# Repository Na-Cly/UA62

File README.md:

# UA62
A Universal PCB for the atreus62 by profet23
#### Firmware availble on the qmk configurator or the qmk repo: 
* https://github.com/qmk/qmk_firmware
* https://config.qmk.fm/#/ua62/LAYOUT (default layout to come)
* no default layout, so grab the json layout and upload it if you want a base layout to start from.

#### Build tips
* Diode direction for through hole  

* The pro micro and diodes are soldered to the bottom of the pcb.  
 
### Changes
1. Added universal switch holes for MX/Alps, Matias/Choc
2. Added support for through-hole diodes
3. Fixed edge cuts: They were off center from the middle of the pcb.
4. Rounded the sharp corners.
5. Uncomplicated the trace layout.
6. Updated pinout for pro micro.
7. Updated Silkscreen.

Uses MIT licensed footprints originally sourced from here: https://github.com/keebio/Keebio-Parts.pretty

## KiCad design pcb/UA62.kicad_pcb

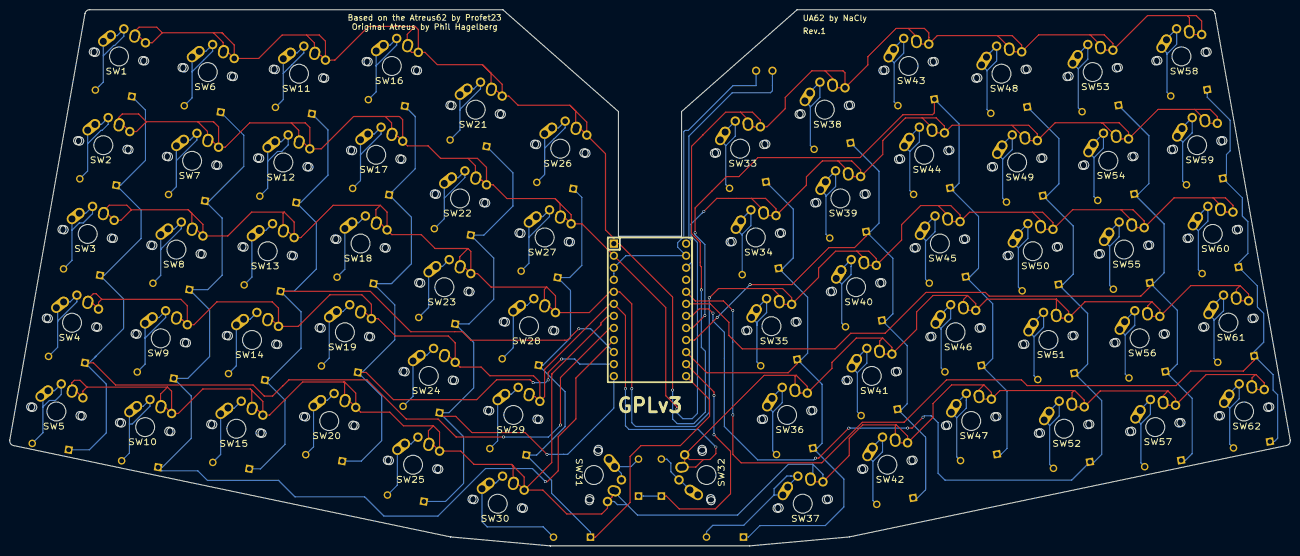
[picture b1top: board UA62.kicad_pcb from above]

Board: 2 copper layers, 270.0 x 113.0 mm, 128 parts (1 on the bottom side), 82 nets.

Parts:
D1, D2, D3, D4, D5, D6, D7, D8, D9, D10, D11, D12, D13, D14, D15, D16, D17, D18, D19, D20, D21, D22, D23, D24, D25, D26, D27, D28, D29, D30, D31, D32, D33, D34, D35, D36, D37, D38, D39, D40, D41, D42, D43, D44, D45, D46, D47, D48, D49, D50, D51, D52, D53, D54, D55, D56, D57, D58, D59, D60, D61, D62: DIODE; Diode-Hybrid-Back
J6, J6#2: D2; SinglePad
SW1, SW2, SW3, SW4, SW5, SW6, SW7, SW8, SW9, SW10, SW11, SW12, SW13, SW14, SW15, SW16, SW17, SW18, SW19, SW20, SW21, SW22, SW23, SW24, SW25, SW26, SW27, SW28, SW29, SW30, SW31, SW32, SW33, SW34, SW35, SW36, SW37, SW38, SW39, SW40, SW41, SW42, SW43, SW44, SW45, SW46, SW47, SW48, SW49, SW50, SW51, SW52, SW53, SW54, SW55, SW56, SW57, SW58, SW59, SW60, SW61, SW62: SWITCH_PUSH; MX-Alps-Choc-1U-NoLED
SW-RST1: SWITCH_PUSH; SW_SPST_B3U-1000P
U1: ARDUINO_PRO_MICRO

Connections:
/COL0: D1.2, D2.2, D3.2, D4.2, D5.2, U1.8
/COL1: D6.2, D7.2, D8.2, D9.2, D10.2, U1.9
/COL2: D11.2, D12.2, D13.2, D14.2, D15.2, U1.10
/COL3: D16.2, D17.2, D18.2, D19.2, D20.2, U1.11
/COL4: D21.2, D22.2, D23.2, D24.2, D25.2, U1.12
/COL5: D26.2, D27.2, D28.2, D29.2, D30.2, U1.13
/COL6: D31.2, D32.2, U1.14
/COL7: D33.2, D34.2, D35.2, D36.2, D37.2, U1.15
/COL8: D38.2, D39.2, D40.2, D41.2, D42.2, U1.16
/COL9: D43.2, D44.2, D45.2, D46.2, D47.2, U1.17
/COL10: D48.2, D49.2, D50.2, D51.2, D52.2, U1.18
/COL11: D53.2, D54.2, D55.2, D56.2, D57.2, U1.19
/COL12: D58.2, D59.2, D60.2, D61.2, D62.2, U1.20
/ROW0: SW5.1, SW10.1, SW15.1, SW20.1, SW25.1, SW30.1, SW31.1, SW37.1, SW42.1, SW47.1, SW52.1, SW57.1, SW62.1, U1.7
/ROW1: SW4.1, SW9.1, SW14.1, SW19.1, SW24.1, SW29.1, SW32.1, SW36.1, SW41.1, SW46.1, SW51.1, SW56.1, SW61.1, U1.6
/ROW2: SW3.1, SW8.1, SW13.1, SW18.1, SW23.1, SW28.1, SW35.1, SW40.1, SW45.1, SW50.1, SW55.1, SW60.1, U1.5
/ROW3: SW2.1, SW7.1, SW12.1, SW17.1, SW22.1, SW27.1, SW34.1, SW39.1, SW44.1, SW49.1, SW54.1, SW59.1, U1.2
/ROW4: SW1.1, SW6.1, SW11.1, SW16.1, SW21.1, SW26.1, SW33.1, SW38.1, SW43.1, SW48.1, SW53.1, SW58.1, U1.1
GND: J6.1, SW-RST1.1, U1.3, U1.4, U1.23
unnamed: D1.1, SW1.2
unnamed: D2.1, SW2.2
unnamed: D3.1, SW3.2
unnamed: D4.1, SW4.2
unnamed: D5.1, SW5.2
unnamed: D6.1, SW6.2
unnamed: D7.1, SW7.2
unnamed: D8.1, SW8.2
unnamed: D9.1, SW9.2
unnamed: D10.1, SW10.2
unnamed: D11.1, SW11.2
unnamed: D12.1, SW12.2
unnamed: D13.1, SW13.2
unnamed: D14.1, SW14.2
unnamed: D15.1, SW15.2
unnamed: D16.1, SW16.2
unnamed: D17.1, SW17.2
unnamed: D18.1, SW18.2
unnamed: D19.1, SW19.2
unnamed: D20.1, SW20.2
unnamed: D21.1, SW21.2
unnamed: D22.1, SW22.2
unnamed: D23.1, SW23.2
unnamed: D24.1, SW24.2
unnamed: D25.1, SW25.2
unnamed: D26.1, SW26.2
unnamed: D27.1, SW27.2
unnamed: D28.1, SW28.2
unnamed: D29.1, SW29.2
unnamed: D30.1, SW30.2
unnamed: D31.1, SW31.2
unnamed: D32.1, SW32.2
unnamed: D33.1, SW33.2
unnamed: D34.1, SW34.2
unnamed: D35.1, SW35.2
unnamed: D36.1, SW36.2
unnamed: D37.1, SW37.2
unnamed: D38.1, SW38.2
unnamed: D39.1, SW39.2
unnamed: D40.1, SW40.2
unnamed: D41.1, SW41.2
unnamed: D42.1, SW42.2
unnamed: D43.1, SW43.2
unnamed: D44.1, SW44.2
unnamed: D45.1, SW45.2
unnamed: D46.1, SW46.2
unnamed: D47.1, SW47.2
unnamed: D48.1, SW48.2
unnamed: D49.1, SW49.2
unnamed: D50.1, SW50.2
unnamed: D51.1, SW51.2
unnamed: D52.1, SW52.2
unnamed: D53.1, SW53.2
unnamed: D54.1, SW54.2
unnamed: D55.1, SW55.2
unnamed: D56.1, SW56.2
unnamed: D57.1, SW57.2
unnamed: D58.1, SW58.2
unnamed: D59.1, SW59.2
unnamed: D60.1, SW60.2
unnamed: D61.1, SW61.2
unnamed: D62.1, SW62.2
unnamed: J6#2.1, SW-RST1.2, U1.22

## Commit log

2019-11-06 Added PCB files
    Uploaded PCB files

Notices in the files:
pcb/UA62.kicad_pcb:
GPLv3
